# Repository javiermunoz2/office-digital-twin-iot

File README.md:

# Office digital twin: IoT environmental monitoring

A digital twin of an office floor. A custom ESP32 sensor node measures temperature, humidity, CO₂, gas/VOC and ambient noise. **ThingsBoard** receives the telemetry and raises alarms, and **n8n** automates storing the history in PostgreSQL. A web dashboard shows the live state of the building on a map and includes a **virtual assistant**, backed by an LLM, that answers questions about current and historical conditions.

> Built during my internship (Nov 2025 – Jan 2026). It covers the full stack: hardware and PCB design, firmware, IoT platform, data pipeline, frontend and LLM integration.

## Architecture

```
 ┌───────────────────────┐   HTTP /telemetry   ┌──────────────┐  alarms / REST API  ┌──────────────────────┐
 │ ESP32 sensor node     │ ──────────────────▶ │ ThingsBoard  │ ◀─────────────────▶ │ n8n workflows        │
 │ SCD41 · MQ-2 · INMP441│                     │ (IoT platform│                     │ · ingest → Postgres  │
 └───────────────────────┘                     │  + alarms)   │                     │ · dashboard webhook  │
 ┌───────────────────────┐   MQTT              └──────────────┘                     │ · chatbot webhook    │
 │ Python simulator      │ ──────────────────▶        ▲                             └──────────┬───────────┘
 │ (public dataset)      │                            │                                        │
 └───────────────────────┘                            │ REST (exporter ETL)          ┌─────────▼─────────┐
                                                      └────────────────────────────▶ │ PostgreSQL        │
 ┌──────────────────────────────────────────┐                                        │ 1-min readings +  │
 │ Web dashboard (Leaflet map, live KPIs,   │ ◀── n8n webhooks ── LLM assistant ◀─── │ 30-min / daily    │
 │ building alarm status, chat assistant)   │                    (Gemini, Qdrant)    │ aggregate views   │
 └──────────────────────────────────────────┘                                        └───────────────────┘
```

## Components

### 1. Hardware: ESP32 sensor node (`hardware/`, `firmware/`)

| Sensor | Measures | Interface |
|---|---|---|
| **SCD41** (Sensirion) | CO₂ (ppm), temperature, humidity | I²C (GPIO 21/22) |
| **MQ-2** | Gas / VOC (analog level) | ADC1, GPIO 34, through a 5 V → 3.3 V voltage divider |
| **INMP441** | Ambient noise (dB) | I²S (GPIO 14/15/32) |

- **Custom PCB** designed in KiCad (`hardware/pcb/`): a carrier board for the ESP32 with connectors for the three sensors, and Gerber and drill files ready for fabrication.
- **Firmware** (`firmware/main/`, Arduino/ESP32) with a modular structure: `sensores.*` for acquisition, `red.*` for Wi-Fi and HTTP, and `config.h` for configuration.
  - **Non-blocking main loop.** It uses `millis()` timers instead of `delay()`, so no sensor readings are lost while the node waits between transmissions.
  - **Noise level.** Computed from the I²S signal amplitude and converted to dB. Audio is never recorded.
  - **Gas filtering.** The gas reading is the average of 50 ADC samples, which filters out the noise induced by the Wi-Fi radio.
  - **Robust networking.** Automatic Wi-Fi reconnection, a 3-second HTTP timeout, and a JSON payload built in a static buffer (no `String`s, to avoid heap fragmentation).

### 2. IoT platform: ThingsBoard

The device sends telemetry to ThingsBoard's HTTP API. ThingsBoard stores the time series and evaluates **alarm rules**, for example high CO₂. Active alarms are shown on the dashboard.

### 3. Data pipeline and storage (`services/`, `database/`)

- **n8n** workflows:
  - Store one reading per minute in PostgreSQL.
  - Expose a webhook with the latest telemetry and alarms for the dashboard.
  - Expose a webhook for the chat assistant.
- **PostgreSQL schema** (`database/schema.sql`): a raw table `lecturas_sensores`, which is the ML-ready history, plus **30-minute** and **daily** aggregate views. The assistant uses these views to answer questions about recent and historical conditions without scanning the raw data.
- **Python services**, used in the first, simulated stage of the project:
  - `publisher`: replays the public UCI *Occupancy Detection* office dataset to ThingsBoard over MQTT, acting as a virtual sensor before the hardware existed.
  - `ingestor`: a debug subscriber that prints the MQTT messages it receives.
  - `exporter`: an ETL job that downloads 30 days of telemetry through the ThingsBoard REST API, aligns the variables by timestamp with pandas and loads them into PostgreSQL.
- `analysis/extraccion_datos.ipynb`: reads the history from PostgreSQL and converts timestamps from UTC to Europe/Madrid, as preparation for ML.

### 4. Frontend (`frontend/index.html`)

A single-page dashboard with a dark theme. It shows:
- A **Leaflet map** with the building's location.
- Live **KPI cards**: temperature, humidity, CO₂, VOC and noise, refreshed every 2 seconds.
- A **building status panel** that turns red when a ThingsBoard alarm is active.
- A **chat assistant** that answers in natural language using the stored data (an LLM called from n8n).

## Tech stack

`ESP32` · `Arduino C++` · `KiCad` · `ThingsBoard` · `MQTT (paho, Mosquitto)` · `n8n` · `PostgreSQL` · `Qdrant` · `Google Gemini` · `Python (pandas, SQLAlchemy, requests)` · `Docker Compose` · `HTML/CSS/JS + Leaflet`

## Running it

```bash
cp .env.example .env               # fill in your own passwords
docker compose up -d               # ThingsBoard :8080, n8n :6789, Postgres, Adminer, Qdrant
```

1. In ThingsBoard, create a device and copy its access token.
2. **Real sensor**: copy `firmware/main/config.example.h` to `config.h`, fill in your Wi-Fi details and the device token, and flash the board with the Arduino IDE. It needs the ESP32 core and the *SparkFun SCD4x Arduino Library*.
   **Simulated sensor**: run `services/publisher` with `MQTT_ACCESS_TOKEN` set.
3. Create the n8n workflows (ingestion, dashboard webhook `estado_oficina`, chat webhook `chat_oficina2`) and add the LLM API key as an **n8n credential**.
4. Open `frontend/index.html` in a browser.

## Repository structure

```
firmware/main/        ESP32 firmware (config.example.h → config.h)
hardware/pcb/         KiCad project + Gerber/drill files
services/             publisher (simulator), ingestor (debug), exporter (ETL)
database/schema.sql   PostgreSQL table + aggregate views
frontend/index.html   Dashboard + chat assistant
analysis/             Data extraction notebook
data/                 Public dataset used for simulation (see data/README.md)
docker-compose.yml    ThingsBoard, n8n, PostgreSQL, Adminer, Qdrant
```

## Author

Javier Muñoz Vera

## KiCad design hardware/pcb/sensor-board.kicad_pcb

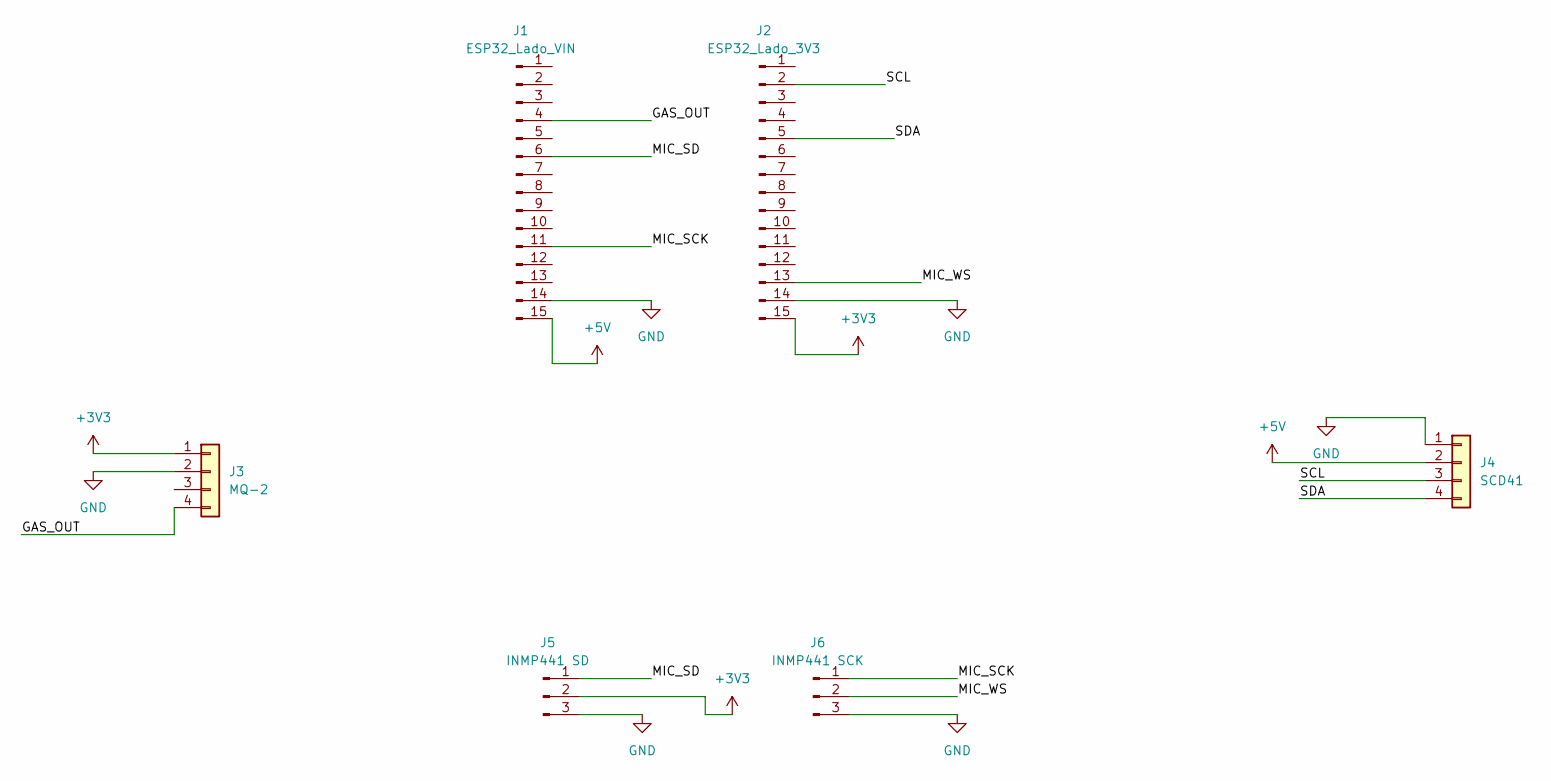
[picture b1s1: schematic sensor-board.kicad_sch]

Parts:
J1: ESP32_Lado_VIN; PinSocket_1x15_P2.54mm_Vertical
J2: ESP32_Lado_3V3; PinSocket_1x15_P2.54mm_Vertical
J3: MQ-2; PinHeader_1x04_P2.54mm_Vertical
J4: SCD41; PinHeader_1x04_P2.54mm_Horizontal
J5: INMP441 SD; PinHeader_1x03_P2.54mm_Vertical
J6: INMP441 SCK; PinHeader_1x03_P2.54mm_Vertical

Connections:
+3V3: J2.15, J3.1, J5.2
+5V: J1.15, J4.2
/GAS_OUT: J1.4, J3.4
/MIC_SCK: J1.11, J6.1
/MIC_SD: J1.6, J5.1
/MIC_WS: J2.13, J6.2
/SCL: J2.2, J4.3
/SDA: J2.5, J4.4
GND: J1.14, J2.14, J3.2, J4.1, J5.3, J6.3

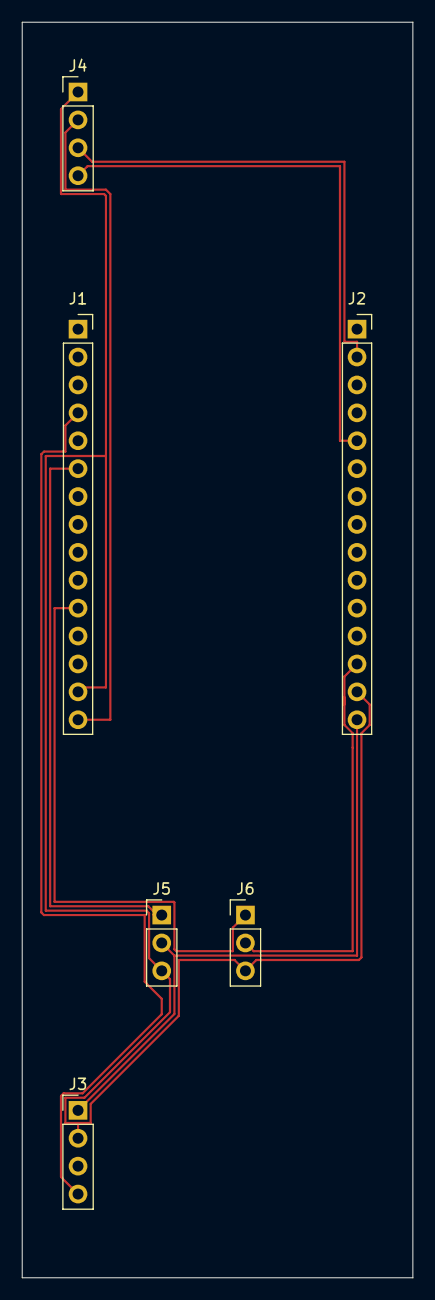
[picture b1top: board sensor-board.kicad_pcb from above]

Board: 2 copper layers, 35.6 x 114.3 mm, 6 parts (0 on the bottom side), 9 nets.
